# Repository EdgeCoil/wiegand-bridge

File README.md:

# Wiegand Bridge

Connect a standard **Wiegand keypad or card reader** to **Home Assistant**.

The reader plugs into this board, and the board sends every PIN and card it sees to Home Assistant
over Wi-Fi (ESPHome). Your automations decide what happens next: unlock a door, disarm an alarm,
or just log who came in.

> **Status: revision 10 is built, tested and working.** The files here are **revision 12**, which
> is routed and checked but not yet ordered: it adds a red/green status LED pair, cleans up the
> silkscreen, and moves the reader monitor and the RS-485 transceiver to integrated parts (see
> [`docs/design.md`](docs/design.md)). The tested design is tag
> [`rev-10b`](https://github.com/EdgeCoil/wiegand-bridge/tree/rev-10b).

## Why it only reports

**The board never unlocks anything.** It has no output to a lock. The reader sits outside the door
where anyone can reach it, so the part that actually opens the door stays inside, behind Home
Assistant. Prising the board off the wall and shorting wires opens nothing.

A stolen board can still give away your Wi-Fi passphrase and its Home Assistant API key, which
are in its flash. [`docs/design.md`](docs/design.md) (*Security — assume it gets stolen*) covers
the precautions: an isolated IoT network, checking the event's `device_id` in your automation, and
alerting on the tamper switch.

## How it works

```
 keypad / card reader ──Wiegand──▶ Wiegand Bridge ──Wi-Fi──▶ Home Assistant ──▶ your lock, alarm, …
          ▲                                │                       │
          └──── beep + LED feedback ◀──────┴──── "granted" / "denied" ┘
```

1. Someone enters a PIN (4–10 digits, then `#`) or presents a card.
2. The board sends a Home Assistant event, `esphome.wiegand_bridge`, with `type` set to `code` or
   `fob` and the PIN or card number in `value`.
3. Your automation checks it and does whatever you want.
4. It calls `feedback_granted` or `feedback_denied` on the board. *Granted* pulses the reader's LED
   three times and then holds it for 3 s; *denied* beeps three times. Both show on the screen, if fitted.

The keypad also works as a **doorbell**: pressing `#` with nothing typed fires the board's
`doorbell` event entity. While someone types, the board's `entry` sensor shows one `*` per digit
(never the digits). `*` clears an entry, and an entry too short to submit is cleared rather than
joined to the next one.

A minimal automation:

```yaml
triggers:
  - trigger: event
    event_type: esphome.wiegand_bridge
    event_data: { type: code }
conditions:
  - condition: template
    value_template: "{{ trigger.event.data.value == states('input_text.door_pin') }}"
actions:
  - action: esphome.wiegand_bridge_feedback_granted
  - action: lock.unlock
    target: { entity_id: lock.front_door }
```

## Getting started

1. **Order the board** (see [Ordering](#ordering)). JLCPCB assembles almost everything.
2. **Wire the reader** to the reader terminals: J3 (`+12V`, `GND`), J10 (`D0`, `D1`) and J11 (`LED`,
   `BEEP`, optional). Set the reader to 26-bit Wiegand. Wire colours vary between readers, so follow
   your reader's own leaflet. The full connector list is in [`docs/design.md`](docs/design.md).
3. **Power it** from 6–36 V (screw terminal or 5.5 mm barrel jack, centre positive), or from USB-C on
   the bench.
4. **Flash the firmware** over USB-C with ESPHome: [`firmware/wiegand-bridge.yaml`](firmware/wiegand-bridge.yaml).
   It needs four entries in your `secrets.yaml`: `wifi_ssid`, `wifi_password`,
   `wiegand_bridge_api_key` and `wiegand_bridge_ota_password`. If you've fitted the OLED, uncomment
   the `packages:` block at the end so it includes [`wiegand-bridge-oled.yaml`](firmware/wiegand-bridge-oled.yaml).
5. **Adopt it in Home Assistant** (ESPHome integration) and write your automation.

For the first power-up, follow the staged bench tests at the end of [`docs/design.md`](docs/design.md).

## Features

**Reader**
- Wiegand D0/D1 through a 5 V-tolerant Schmitt buffer, clamped against 12 V miswiring
- Open-drain LED and BEEP outputs back to the reader
- RS-485 port (THVD1420, fail-safe receiver) for OSDP readers, with jumper-selectable termination and bias

**Power**
- 6–36 V input, reverse-polarity and surge protected
- Regulated reader supply from every power source: 12.6 V (13.2 V by solder jumper), with current
  and voltage monitoring (INA226) and firmware-controlled shedding
- LiFePO4 backup: on-board charger (CN3058E, 3.6 V), cell protection (DW01A + FS8205A),
  thermistor-gated charging, seamless handover when external power drops

**Sensing and display**
- Tamper switch under the lid, plus a header for an enclosure-mounted one
- Four dry-contact inputs (door contact, exit button and so on), 24 V-tolerant
- Socket for a 1.3" SH1106 OLED (I²C), plus an SPI header for a TFT or e-paper

**Brains and expansion**
- ESP32-S3-WROOM-1-N8R2 with Wi-Fi and BLE; native USB-C for flashing and logs
- Status LEDs: red `FAULT` (warnings and errors) and green `OK` (connected to Home Assistant)
- TCA9535 expander for status lines and spares; Qwiic, W5500 Ethernet and 2×6 expansion headers
- SM712 surge and ESD protection on every field wire
- Optional relay footprint, **not fitted** by default (see *Security* in the design doc)

**Board:** 90 × 95 mm, 4 layers, assembled by JLCPCB.

## LITE (in development)

A 42 × 47 mm sibling for readers that already have their own supply: ESP32-S3-MINI-1, 8–16 V in,
USB-C, one 8-way pluggable terminal, and RS-485. Its D0/D1/LED/BEEP lines all work both ways, so it
can also pretend to be a reader towards an existing access controller.

**Designed, routed and checked, but no board made yet.** See [`docs/lite.md`](docs/lite.md),
[`hardware/lite/`](hardware/lite/) and [`firmware/wiegand-bridge-lite.yaml`](firmware/wiegand-bridge-lite.yaml).

| LITE | Next to the full board |
|---|---|
|  |  |

## What's in this repository

| Path | What it is |
|---|---|
| [`firmware/`](firmware/) | ESPHome configurations: the full board and its optional OLED package, the LITE, and a bench-only LITE emulation package |
| [`docs/design.md`](docs/design.md) | How it works, pin map, connectors, security notes and bench tests |
| [`docs/breadboard.md`](docs/breadboard.md) | A through-hole breadboard version, for trying your reader before ordering |
| [`docs/lite.md`](docs/lite.md) | The LITE board in detail |
| [`hardware/`](hardware/) | The board, **generated from Python** (`netlist.py` is the source of truth) |
| [`hardware/fab/`](hardware/fab/) | Ready-to-order files: Gerbers, BOM, placement, schematic and assembly PDFs, renders |
| [`hardware/sim/`](hardware/sim/) | ngspice checks of the analogue corners |
| [`hardware/lite/`](hardware/lite/) | The LITE board's scripts and outputs |

## Ordering

1. Upload `hardware/fab/wiegand-bridge-gerbers.zip` to JLCPCB and choose **4 layers** with
   **inner copper weight 1 oz**. JLCPCB's default for the inner layers is 0.5 oz, and the power rails
   and battery paths on In2 are sized for 1 oz (see *Layout* in the design doc).
2. Turn on **PCB Assembly**, top side, and upload `wiegand-bridge-bom.csv` and `wiegand-bridge-cpl.csv`.
3. **Check every polarised part in the placement preview** before confirming: diodes, LEDs, ICs,
   the ESP32 and the USB-C. Look especially at the status LEDs D8 and D23 (D8 changed footprint
   family in rev 11), U12 (INA226, MSOP-10), U9 (THVD1420), and the new U13 (TPS26625, VSON-10,
   0.5 mm pitch with an exposed pad; pin 1 top-left at rotation 0) and Q5 (DMP2035U, SOT-23).

JLCPCB doesn't fit the battery connector housing and cell, the OLED module, the barrel jack J14, or
any unpopulated headers. Add those yourself. J14's footprint is the DC-005 5.5 × 2.0 mm jack (LCSC
C16214), which LCSC lists at 12 V, 1 A: above 12 V use the screw terminal J2, or fit a jack rated
for your supply.

## Rebuilding the board

Everything under `hardware/` is produced by scripts, so the board can be rebuilt after any change.

| Script | What it does |
|---|---|
| `netlist.py` | Every part, its JLCPCB part number, and which net each pad joins |
| `placement.py` | Where each part sits |
| `build_pcb.py` | Makes `wiegand-bridge.kicad_pcb`, unrouted, from the two files above |
| `route.py` | Thermal vias, hand routes for the fine-pitch parts, GND fan-out, Freerouting, pours; fails on anything unconnected |
| `freeze.py`, `routing.json` | The frozen routing (since rev 12): `save` records the finished board's tracks and vias, `replay` lays them back |
| `padgap.py` | Pre-route: pads of different nets closer than 0.25 mm |
| `kelvin.py` | The reader shunt's Kelvin connection (net-tied sense tabs, own sense nets) |
| `stitch.py`, `via_fix.py`, `gndcheck.py`, `dfm_post.py`, `audit.py` | Stitching, vias out of pads, ground connectivity, paste and pours, mechanical and current audit |
| `finish_net.py` | Routes one straggling connection by grid A* if Freerouting leaves one |
| `schematic.py` | A readable schematic PDF from the netlist |
| `fab.py` | JLCPCB outputs into `fab/` |

The routing is **frozen**: `routing.json` holds every track and via of the reviewed board and a
rebuild replays it, so a fix is a small edit to that file rather than a new layout.

```bash
cd hardware
python3 build_pcb.py                       # needs KiCad 9's pcbnew Python module
python3 freeze.py replay                   # lay routing.json's copper back, rebuild the pours
python3 dfm_post.py
python3 kelvin.py                          # the shunt's sense lines are on their own copper
python3 gndcheck.py && python3 audit.py && python3 fab.py
kicad-cli pcb drc wiegand-bridge.kicad_pcb
```

Routing afresh, only when placement changes (the next review then covers all copper):

```bash
cd hardware
python3 build_pcb.py
python3 padgap.py 0.25                     # must report 0 pad pairs before routing
ROUTE_WORK=/tmp/wb python3 route.py 60     # needs Java + Freerouting 2.4.x; exits non-zero if anything is unconnected
python3 stitch.py && python3 stitch.py --islands
python3 via_fix.py --apply && python3 via_fix.py   # the second run must report 0 vias inside pad openings
python3 gndcheck.py
python3 dfm_post.py
python3 kelvin.py
python3 audit.py
python3 fab.py
kicad-cli pcb drc wiegand-bridge.kicad_pcb
python3 freeze.py save                     # record the copper in routing.json
```

Tools: KiCad 9.0, Freerouting 2.4.1 (OpenJDK), `easyeda2kicad` 1.0.1 (for `lib/`), ngspice 44.

<details>
<summary>3D models (not included)</summary>

The models come to about 60 MB, so they aren't in the repository, and the renders in `fab/` show
only the 0603/0805 passives: every other part renders as bare pads. To fetch them, run `easyeda2kicad --3d --lcsc_id=<part> --output hardware/lib/wb`
for the LCSC part numbers in the BOM. The 0603/0805 passives use KiCad's stock footprints, whose
models come from `kicad-packages3d`: `fab.py` looks for them in `~/.local/share/kicad/9.0/3dmodels`
(three files: `Resistor_SMD.3dshapes/R_0603_1608Metric`, `Capacitor_SMD.3dshapes/C_0603_1608Metric`
and `C_0805_2012Metric`, `.step` + `.wrl`, from gitlab.com/kicad/libraries/kicad-packages3D).

</details>

## Licence

| What | Licence |
|---|---|
| The board: everything in `hardware/`, including the scripts that define it (`netlist.py`, `placement.py`, `build_pcb.py`, `route.py`), the simulations and the fabrication outputs | [CERN-OHL-S-2.0](LICENSES/CERN-OHL-S-2.0.txt) |
| Firmware and the general-purpose build tools (every other script in `hardware/`) | [MIT](LICENSES/MIT.txt) |
| Documentation (`README.md`, `docs/`) and the renders | [CC BY 4.0](LICENSES/CC-BY-4.0.txt) |

Each source file carries an SPDX header, and [`REUSE.toml`](REUSE.toml) covers the rest by path.

CERN-OHL-S is strongly reciprocal. You may build, modify and sell boards from this design, but if
you ship a modified version you must publish its source under the same licence. The source lives at
https://github.com/EdgeCoil/wiegand-bridge, linked from the board's back silkscreen as
`wiegand.edgecoil.dev`.

**The edgecoil name and mark are not licensed.** Remove the mark from the silkscreen of any boards
you make or sell, and don't sell them under the edgecoil name.

The design is provided as is, with no warranty. It is an access-control accessory, so you are
responsible for the security of any installation.

---

edgecoil · [edgecoil.dev](https://edgecoil.dev)

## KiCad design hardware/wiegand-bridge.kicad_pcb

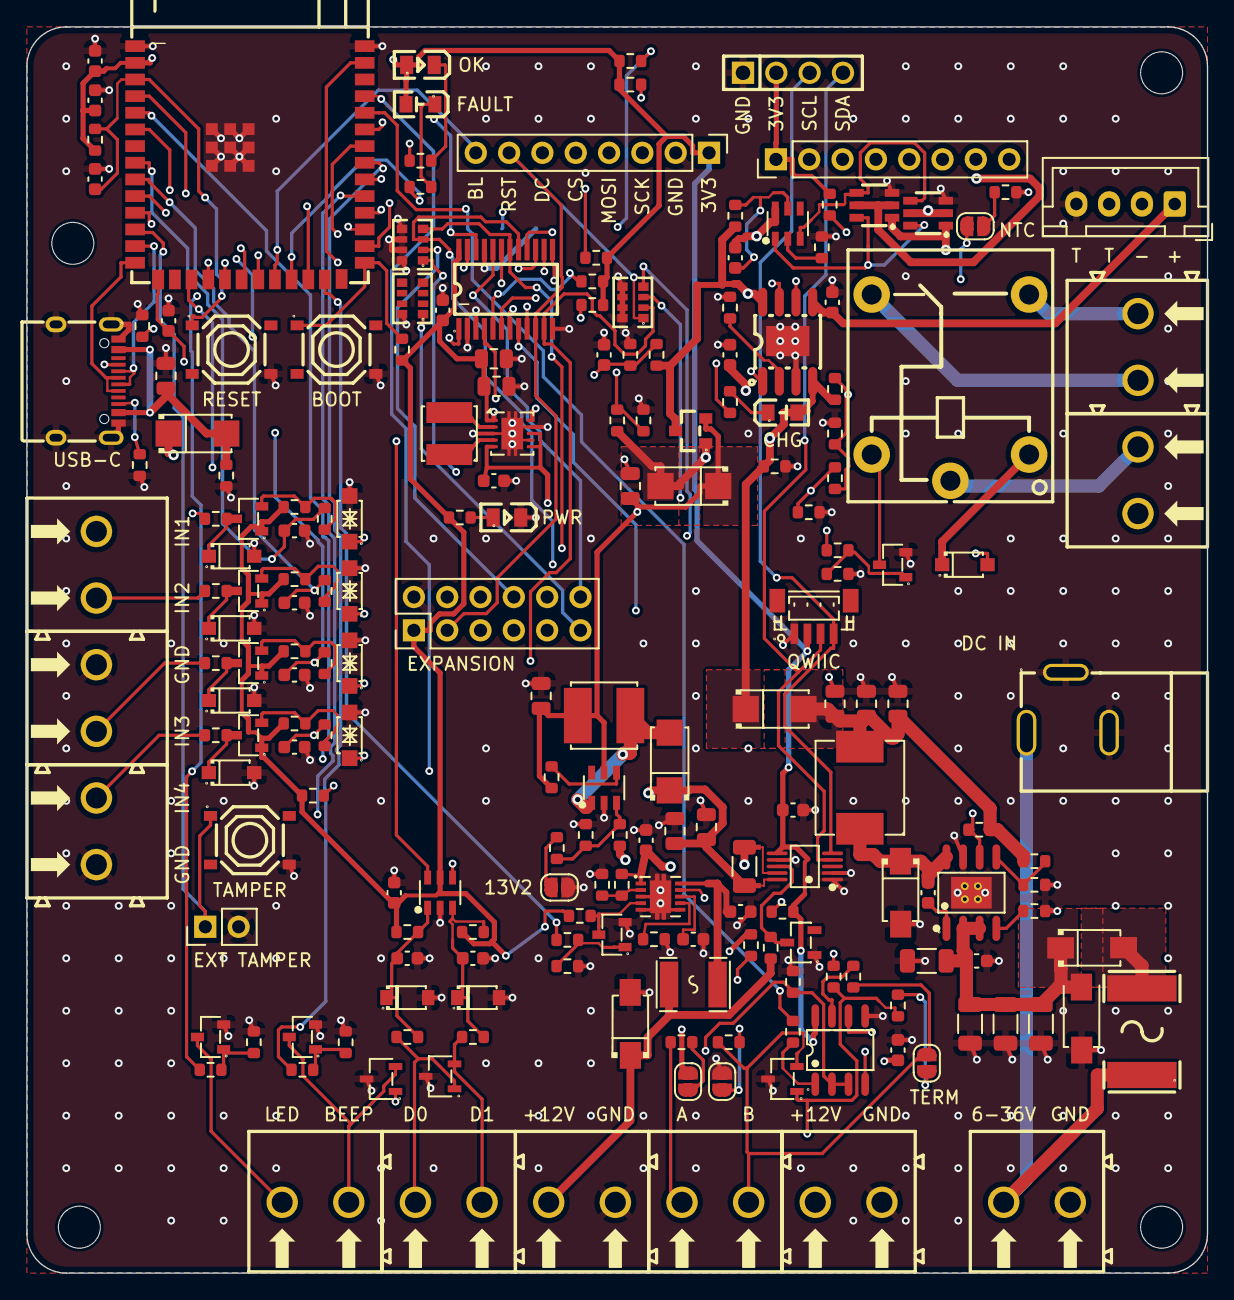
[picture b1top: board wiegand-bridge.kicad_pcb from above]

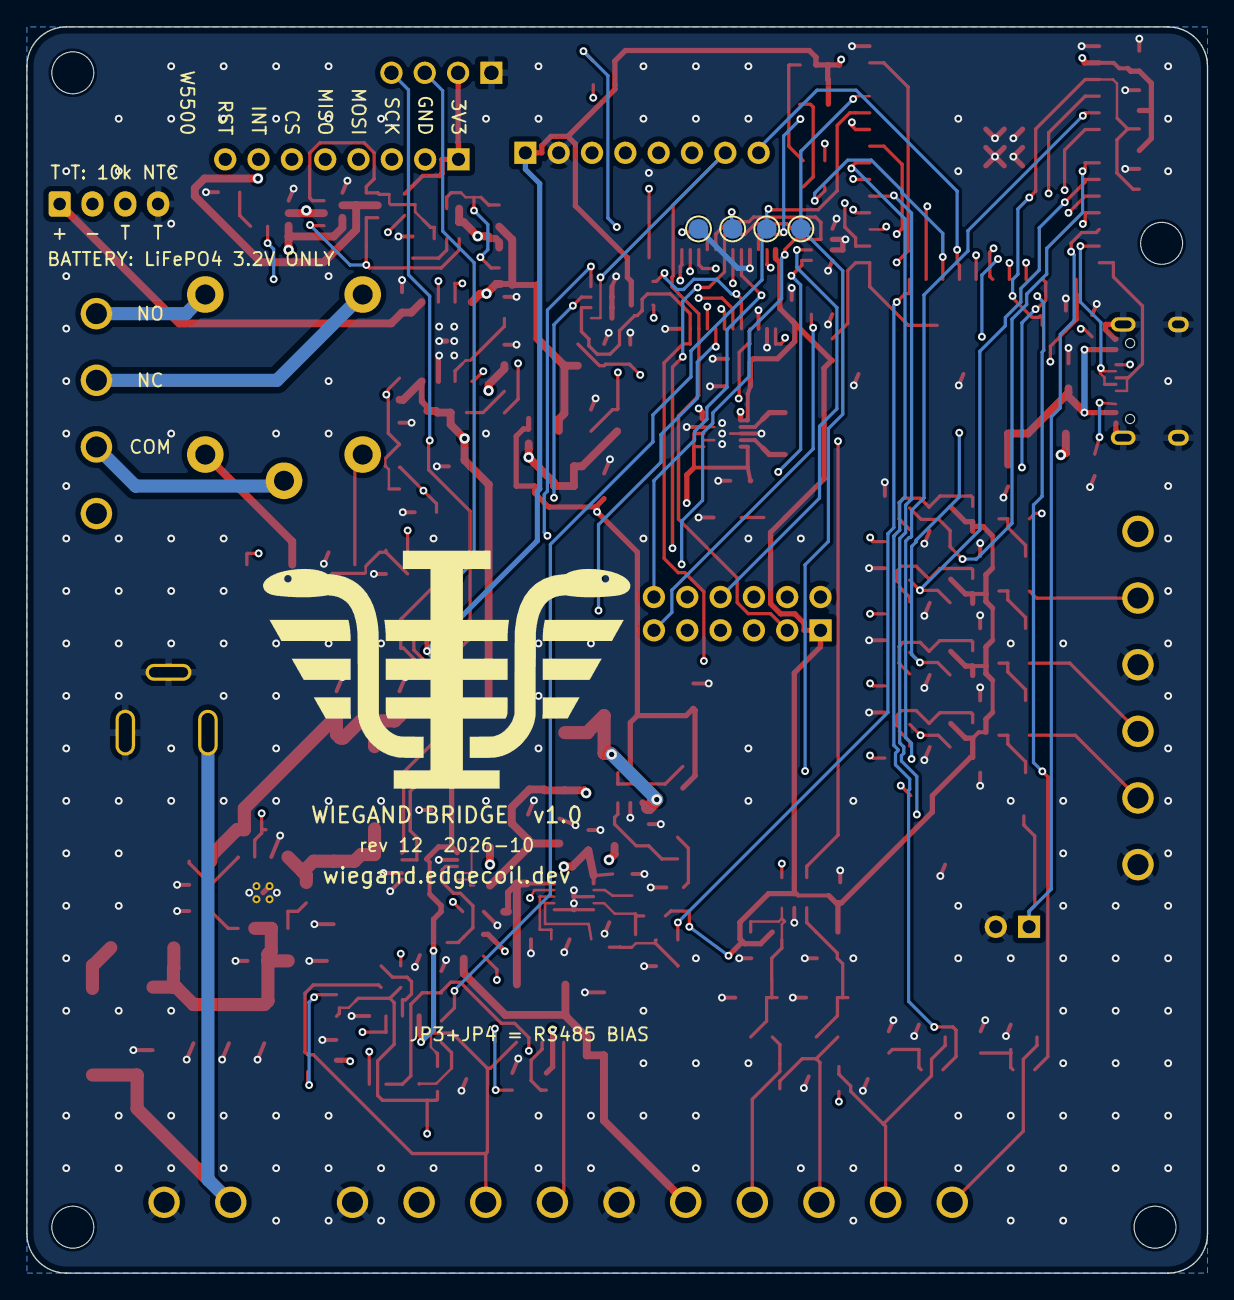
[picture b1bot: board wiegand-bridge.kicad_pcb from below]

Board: 4 copper layers, 90.0 x 95.0 mm, 208 parts (4 on the bottom side), 129 nets.

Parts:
C2, C31, C32, C33: 10u; C_1206_3216Metric
C3, C12, C16, C22, C23, C34, C36, C37, C39, C40, C41, C43: 100n; C_0603_1608Metric
C4, C5, C7, C9, C10, C17, C18, C19, C35: 22u; C_0805_2012Metric
C6: 10u; C_0805_2012Metric
C8, C20, C21: 10u; C_0603_1608Metric
C11: 22u; C_0603_1608Metric
C13: 1u; C_0603_1608Metric
C14, C15: 100p; C_0603_1608Metric
C27, C28, C29, C30: 10n; C_0603_1608Metric
C42: 680n; C_0603_1608Metric
D1, D13: SS56; SMA_L4.3-W2.6-LS5.0-RD
D2: SMAJ36CA; SMA_L4.3-W2.6-LS5.0-BI
D3, D4, D10, D11: SS34; SMA_L4.3-W2.6-LS5.2-RD
D5, D6: MMSZ5231B; SOD-123_L2.8-W1.6-LS3.7-RD
D7, D23: green; LED0805-R-RD
D8, D12: red; LED0805-RD
D14, D28, D29, D30, D31: 1N4148W; SOD-123F_L2.7-W1.6-LS3.8-RD
D15, D16, D19: SM712; SOT-23-3_L3.0-W1.7-P0.95-LS2.9-BR
D17, D18, D21, D22: SMF36CA; SOD-123FL_L2.7-W1.8-LS3.8-BI
D20: SMAJ15A; SMA_L4.3-W2.6-LS5.0-RD
D27: BAT54; SOT-23-3_L2.9-W1.4-P1.90-LS2.5-BR
F1: 0.5A; F1812
F2: 2A 60V; F2920
H1, H2, H3, H4: M3; MountingHole_3.2mm_M3
J1: USB-C; USB-C-SMD_TYPE-C-16PIN-2MD-073
J2: 6-36V IN; CONN-TH_P5.08_KF128-5.08-2P
J3: READER PWR; CONN-TH_P5.08_KF128-5.08-2P
J4: LiFePO4 + NTC; JST_XH_B4B-XH-A_1x04_P2.50mm_Vertical
J5: OLED SOCKET; HDR-TH_4P-P2.54-V-F
J6: TFT/EPD; PinHeader_1x08_P2.54mm_Vertical
J8: TAMPER EXT; PinHeader_1x02_P2.54mm_Vertical
J9: IN1 IN2; CONN-TH_P5.08_KF128-5.08-2P
J10: READER D0 D1; CONN-TH_P5.08_KF128-5.08-2P
J11: READER LED BEEP; CONN-TH_P5.08_KF128-5.08-2P
J12: GND IN3; CONN-TH_P5.08_KF128-5.08-2P
J13: IN4 GND; CONN-TH_P5.08_KF128-5.08-2P
J14: DC IN; DC-IN-TH_DC-005-5.5-2.0
J15: RELAY NC NO; CONN-TH_P5.08_KF128-5.08-2P
J16: RELAY COM; CONN-TH_P5.08_KF128-5.08-2P
J17: W5500; PinHeader_1x08_P2.54mm_Vertical
J18: QWIIC; CONN-SMD_BM04B-SRSS-TB
J19: EXPANSION; PinHeader_2x06_P2.54mm_Vertical
J20: RS485 A B; CONN-TH_P5.08_KF128-5.08-2P
J21: RS485 12V GND; CONN-TH_P5.08_KF128-5.08-2P
JP1: 13.2V; SolderJumper-2_P1.3mm_Open_RoundedPad1.0x1.5mm
JP2: TERM; SolderJumper-2_P1.3mm_Open_RoundedPad1.0x1.5mm
JP3, JP4: BIAS; SolderJumper-2_P1.3mm_Open_RoundedPad1.0x1.5mm
JP5: NTC ON BOARD; SolderJumper-2_P1.3mm_Open_RoundedPad1.0x1.5mm
K1: SRD-05VDC-SL-C; RELAY-TH_SRD-XXVDC-XL-C
L1: 15uH; IND-SMD_L7.0-W6.6_FXL0630
L2: 2.2uH; IND-SMD_L4.0-W4.0
L3: 4.7uH; IND-SMD_L5.0-W5.0
Q1, Q2, Q4, Q7, Q8, Q9, Q10: 2N7002; SOT-23-3_L2.9-W1.3-P1.90-LS2.4-BR
Q5: DMP2035U; SOT-23_L2.9-W1.3-P1.90-LS2.4-BR
Q6, Q13: FS8205A; SOT-23-6_L2.9-W1.6-P0.95-LS2.8-BR
Q12: AO3400A; SOT-23-3_L2.9-W1.3-P1.90-LS2.4-BR
R1, R2, R77: 5.1k; R_0603_1608Metric
R3, R81: 470; R_0603_1608Metric
R4, R5, R15, R18, R20, R27, R35, R50, R60, R65, R75, R76, R90, R91, R92, R93, R97: 10k; R_0603_1608Metric
R6, R7, R17, R25: 100; R_0603_1608Metric
R8, R9, R10, R24, R26, R63, R85, R94: 1k; R_0603_1608Metric
R11, R12: 22k; R_0603_1608Metric
R13, R14, R21, R28, R29, R58, R61, R62, R64, R79, R99: 100k; R_0603_1608Metric
R16: 15k; R_0603_1608Metric
R19, R30, R80: 200k; R_0603_1608Metric
R36, R37, R40, R41, R42, R43, R82: 4.7k; R_0603_1608Metric
R44, R45, R46, R47, R56: 47k; R_0603_1608Metric
R51: 1M; R_0603_1608Metric
R55: 39k; R_0603_1608Metric
R57: 8.2k; R_0603_1608Metric
R59: 0.1R; R_1206_Kelvin
R68: 120; R_0603_1608Metric
R72, R73: 390; R_0603_1608Metric
R78: 68k; R_0603_1608Metric
R83, R84: 10; R_0603_1608Metric
R95: 26.7k; R_0603_1608Metric
R96: 120k; R_0603_1608Metric
RN1, RN2, RN3: 4x10k; RES-ARRAY-SMD_0603-8P-L3.2-W1.6-BL
RT1: 10k NTC B3950; R_0603_1608Metric
SW1: BOOT; SW-SMD_4P-L5.1-W5.1-P3.70-LS6.5-TL_H1.5
SW2: RESET; SW-SMD_4P-L5.1-W5.1-P3.70-LS6.5-TL_H1.5
SW3: TAMPER; SW-SMD_4P-L5.1-W5.1-P3.70-LS6.5-TL_H1.5
TP1: RS485_DI; TestPoint_Pad_D1.5mm
TP2: RS485_RXD; TestPoint_Pad_D1.5mm
TP3: IO40; TestPoint_Pad_D1.5mm
TP4: GND; TestPoint_Pad_D1.5mm
U1: ESP32-S3-WROOM-1-N8R2; WIRELM-SMD_ESP32-S3-WROOM-1
U2: LMR16020; SOIC-8_L4.9-W3.9-P1.27-LS6.0-BL-EP
U3: TPS63001; Texas_DRC0010J
U4: SN74LVC2G17; SOT-23-6_L2.9-W1.6-P0.95-LS2.8-BL
U5: CN3058E; SOIC-8_L4.9-W3.9-P1.27-LS6.0-BL-EP3.3
U6: MT3608; SOT-23-6_L2.9-W1.6-P0.95-LS2.8-BL
U7: DW01A; SOT-23-6_L2.9-W1.6-P0.95-LS2.8-BL
U8: TCA9535; TSSOP-24_L7.8-W4.4-P0.65-LS6.4-BL
U9: THVD1420; SOIC-8_L4.9-W3.9-P1.27-LS6.0-BL
U12: INA226; MSOP-10_L3.0-W3.0-P0.50-LS5.0-BL
U13: TPS26625; VSON-10_L3.0-W3.0-P0.50-TL-EP-1

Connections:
+3V3: C9.1, C10.1, C11.1, C12.1, C16.1, C36.1, C37.1, C39.1, D8.2, D23.1, J5.2, J6.1, J17.1, J18.2, J19.1, JP3.2, Q7.1, Q8.1, Q9.1, Q10.1, R3.1, R4.1, R5.1, R11.1, R12.1, R35.1, R36.1, R37.1, R44.1, R45.1, R46.1, R47.1, R60.2, R61.2, R62.2, R75.2, R76.2, R97.2, R99.1, U1.2, U3.1, U3.10, U4.5, U8.24, U9.8, U12.6
+5V: C20.1, D3.1, D4.1, D11.2, D12.2, D14.1, K1.1, Q5.1, R15.1, R27.1, R77.1, U5.4
+5V_BUCK: C4.1, C5.1, C35.1, D3.2, L1.2, R56.1, R58.2
+12V_RDR: D20.1, F1.2, J3.1, J21.1, R82.1
+VIN: C2.1, C31.1, C32.1, C33.1, C34.1, D1.1, D2.1, U2.2, U2.3
+VIN_F: D1.2, F2.2
+VIN_RAW: F2.1, J2.1, J14.4
BAT+: C21.1, J4.1, Q5.3, R25.1, R28.1, U5.5, U5.8
BAT-: C22.2, J4.2, Q6.1, Q13.1, U7.6
BAT_SENSE: C23.1, R28.2, R29.1, U1.39
BAT_TEMP: J4.3, JP5.1, R77.2, R78.1, R79.1, U5.1
BEEP_GATE: Q2.1, R7.2, R14.1
BOOST_FB: R19.2, R20.1, R30.1, U6.3
BOOST_OUT: C18.1, C19.1, D10.1, R19.1, R59.1
BOOST_SNS: C41.1, R51.1, R59.2, U13.1
BOOST_SW: D10.2, L3.2, U6.1
CC1: J1.A5, R1.1
CC2: J1.B5, R2.1
CHRG: R24.1, R61.1, U5.7, U8.5
D0_IN: C14.1, D5.1, R9.2, R11.2, U4.1
D0_RAW: D15.1, J10.1, R9.1
D1_IN: C15.1, D6.1, R10.2, R12.2, U4.3
D1_RAW: D15.2, J10.2, R10.1
D7_A: D7.1, R3.2
D8_K: D8.1, R8.2
D12_K: D12.1, R24.2
D23_K: D23.2, R81.2
DISP_RST: J6.7, J19.3, RN1.1, U8.10
DONE_N: R62.1, U5.6, U8.6
EN: C13.1, R4.2, SW2.1, U1.3
ETH_CS: J17.6, U1.29
ETH_INT: J17.7, U1.30
ETH_MISO: J17.5, U1.28
ETH_RST: J17.8, R76.1, U8.9
EXP07: J19.4, RN1.2, U8.11
EXP10: J19.5, RN1.3, U8.13
EXP11: J19.6, RN1.4, U8.14
EXP12: J19.7, RN2.1, U8.15
EXP13: J19.8, RN2.2, U8.16
EXP14: J19.9, RN2.3, U8.17
EXP15: J19.10, RN2.4, U8.18
EXP16: J19.11, RN3.1, U8.19
EXP17: J19.12, U8.20
EXP_INT: R60.1, U1.32, U8.1
EXT_SENSE: R15.2, R16.1, U8.7
GND: C2.2, C4.2, C5.2, C6.2, C7.2, C8.2, C9.2, C10.2, C11.2, C12.2, C13.2, C14.2, C15.2, C16.2, C17.2, C18.2, C19.2, C20.2, C21.2, C23.2, C27.2, C28.2, C29.2, C30.2, C31.2, C32.2, C33.2, C34.2, C35.2, C36.2, C37.2, C39.2, C40.2, C41.2, C42.2, C43.2, D2.2, D5.2, D6.2, D7.2, D13.2, D15.3, D16.3, D17.2, D18.2, D19.3, D20.2, D21.2, D22.2, D27.1, D28.2, D29.2, D30.2, D31.2, J1.13, J1.14, J1.A1B12, J1.B1A12, J2.2, J3.2, J4.4, J5.1, J6.2, J8.2, J12.1, J13.2, J14.2, J14.3, J17.2, J18.1, J19.2, J21.2, JP1.2, JP4.2, Q1.2, Q2.2, Q4.2, Q6.3, Q12.2, Q13.3, R1.2, R2.2, R13.2, R14.2, R16.2, R18.2, R20.2, R26.2, R27.2, R29.2, R50.2, R55.2, R57.2, R64.2, R65.2, R78.2, R80.2, R94.2, R95.2, R96.2, RN1.5, RN1.6, RN1.7, RN1.8, RN2.5, RN2.6, RN2.7, RN2.8, RN3.8, RT1.2, SW1.4, SW2.4, SW3.4, TP4.1, U1.1, U1.40, U1.41, U2.7, U2.9, U3.3, U3.7, U3.9, U3.11, U4.2, U5.3, U5.9, U6.2, U8.2, U8.3, U8.12, U8.21, U9.5, U12.1, U12.2, U12.7, U13.3, U13.5, U13.6, U13.11
I2C_SCL: J5.3, J18.4, R37.2, U1.35, U8.22, U12.5
I2C_SDA: J5.4, J18.3, R36.2, U1.34, U8.23, U12.4
IN1: C27.1, R90.2, U1.8
IN1_D: D28.1, Q7.3, R40.2
IN1_RAW: D17.1, J9.1, R40.1
IN1_S: Q7.2, R44.2, R90.1
IN2: C28.1, R91.2, U1.9
IN2_D: D29.1, Q8.3, R41.2
IN2_RAW: D18.1, J9.2, R41.1
IN2_S: Q8.2, R45.2, R91.1
IN3: C29.1, R92.2, U1.10
IN3_D: D30.1, Q9.3, R42.2
IN3_RAW: D21.1, J12.2, R42.1
IN3_S: Q9.2, R46.2, R92.1
IN4: C30.1, R93.2, U1.11
IN4_D: D31.1, Q10.3, R43.2
IN4_RAW: D22.1, J13.1, R43.1
IN4_S: Q10.2, R47.2, R93.1
IO0: R5.2, SW1.1, U1.27
IO6: R6.1, U1.6
IO21: R8.1, U1.23
IO40: R7.1, TP3.1, U1.33
IO47: R81.1, U1.24
IO48: R17.1, U1.25
ISET: R50.1, U5.2
ISNS_N: R59.4, U12.9
ISNS_P: R59.3, U12.10
JP1_A: JP1.1, R30.2
JP2_A: JP2.1, R68.2
JP3_A: JP3.1, R72.2
JP4_A: JP4.1, R73.2
LED_GATE: Q1.1, R6.2, R13.1
OC: Q6.4, Q13.4, U7.3
OD: Q6.6, Q13.6, U7.1
PGOOD5: R58.1, U2.6, U8.8
Q4_G: Q4.1, R17.2, R18.1
Q6_D: Q6.2, Q6.5, Q13.2, Q13.5
Q12_G: Q12.1, R63.2, R64.1
RDR_BEEP: D16.2, J11.2, Q2.3
RDR_EN: Q4.3, R99.2, U13.4
RDR_FLT: R97.1, U1.17, U13.9
RDR_LED: D16.1, J11.1, Q1.3
RDR_SW: C43.1, F1.1, U13.10
RDR_VBUS: D27.3, R82.2, U12.8
RELAY_COIL: D14.2, K1.4, Q12.3
RELAY_COM: J16.2, K1.5
RELAY_DRV: R63.1, U8.4
RELAY_NC: J15.1, K1.3
RELAY_NO: J15.2, K1.2
RS485_A: D19.1, J20.1, R68.1, R72.1, R83.1
RS485_B: D19.2, J20.2, JP2.2, R73.1, R84.1
RS485_DE: R65.1, U1.31, U9.2, U9.3
RS485_DI: TP1.1, U1.37, U9.4
RS485_RO: R85.1, U9.1
RS485_RXD: R75.1, R85.2, TP2.1, U1.36
RT1_A: JP5.2, RT1.1
SPI_BL_BUSY: J6.8, U1.22
SPI_CS: J6.5, U1.18
SPI_DC: J6.6, U1.21
SPI_MOSI: J6.4, J17.4, U1.19
SPI_SCK: J6.3, J17.3, U1.20
TAMPER: J8.1, R35.2, SW3.1, U1.12
TEMP_ADC: C40.1, R79.2, R80.1, U1.15
U2_BST: C3.1, U2.1
U2_FB: R56.2, R57.1, U2.5
U2_RT: R55.1, U2.4
U2_SW: C3.2, D13.1, L1.1, U2.8
U3_L1: L2.1, U3.4
U3_L2: L2.2, U3.2
U6_EN: R21.2, U6.4
U7_VCC: C22.1, R25.2, U7.5
U9_A: R83.2, U9.6
U9_B: R84.2, U9.7
U13_DVDT: C42.1, U13.8
U13_ILIM: R95.1, U13.7
U13_UVLO: R51.2, R96.1, U13.2
USB_DN: J1.A7, J1.B7, U1.13
USB_DP: J1.A6, J1.B6, U1.14
VBUS: C6.1, D4.2, J1.A4B9, J1.B4A9, R94.1
VM: R26.1, U7.2
VSYS: C7.1, C8.1, C17.1, D11.1, L3.1, Q5.2, R21.1, U3.5, U3.6, U3.8, U6.5
WG_D0: U1.4, U4.6
WG_D1: U1.5, U4.4

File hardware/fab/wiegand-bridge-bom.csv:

Comment,Designator,Footprint,LCSC Part #
22u,C11,C_0603_1608Metric,C59461
1u,C13,C_0603_1608Metric,C15849
100p,"C14,C15",C_0603_1608Metric,C14858
10n,"C27,C28,C29,C30",C_0603_1608Metric,C57112
10u,"C2,C31,C32,C33",C_1206_3216Metric,C13585
100n,"C3,C12,C16,C22,C23,C34,C36,C37,C39,C40,C41,C43",C_0603_1608Metric,C14663
22u,"C4,C5,C7,C9,C10,C17,C18,C19,C35",C_0805_2012Metric,C45783
680n,C42,C_0603_1608Metric,C107067
10u,C6,C_0805_2012Metric,C15850
10u,"C8,C20,C21",C_0603_1608Metric,C19702
SS56,"D1,D13",SMA_L4.3-W2.6-LS5.0-RD,C18199169
SM712,"D15,D16,D19",SOT-23-3_L3.0-W1.7-P0.95-LS2.9-BR,C32677
SMF36CA,"D17,D18,D21,D22",SOD-123FL_L2.7-W1.8-LS3.8-BI,C19077521
SMAJ36CA,D2,SMA_L4.3-W2.6-LS5.0-BI,C19077551
SMAJ15A,D20,SMA_L4.3-W2.6-LS5.0-RD,C19077535
BAT54,D27,SOT-23-3_L2.9-W1.4-P1.90-LS2.5-BR,C22466368
1N4148W,"D14,D28,D29,D30,D31",SOD-123F_L2.7-W1.6-LS3.8-RD,C81598
SS34,"D3,D4,D10,D11",SMA_L4.3-W2.6-LS5.2-RD,C8678
MMSZ5231B,"D5,D6",SOD-123_L2.8-W1.6-LS3.7-RD,C19077422
green,"D7,D23",LED0805-R-RD,C2297
red,"D8,D12",LED0805-RD,C84256
0.5A,F1,F1812,C516067
2A 60V,F2,F2920,C49326266
USB-C,J1,USB-C-SMD_TYPE-C-16PIN-2MD-073,C2765186
KF128-5.08-2P screw terminal,"J2,J3,J9,J10,J11,J12,J13,J20,J21",CONN-TH_P5.08_KF128-5.08-2P,C474952
LiFePO4 + NTC,J4,JST_XH_B4B-XH-A_1x04_P2.50mm_Vertical,C144395
OLED SOCKET,J5,HDR-TH_4P-P2.54-V-F,C2718488
15uH,L1,IND-SMD_L7.0-W6.6_FXL0630,C177243
2.2uH,L2,IND-SMD_L4.0-W4.0,C279948
4.7uH,L3,IND-SMD_L5.0-W5.0,C305174
2N7002,"Q1,Q2,Q4,Q7,Q8,Q9,Q10",SOT-23-3_L2.9-W1.3-P1.90-LS2.4-BR,C8545
AO3400A,Q12,SOT-23-3_L2.9-W1.3-P1.90-LS2.4-BR,C20917
DMP2035U,Q5,SOT-23_L2.9-W1.3-P1.90-LS2.4-BR,C110499
FS8205A,"Q6,Q13",SOT-23-6_L2.9-W1.6-P0.95-LS2.8-BR,C2830320
5.1k,"R1,R2,R77",R_0603_1608Metric,C23186
22k,"R11,R12",R_0603_1608Metric,C31850
10k,"R4,R5,R15,R18,R20,R27,R35,R50,R60,R65,R75,R76,R90,R91,R92,R93,R97",R_0603_1608Metric,C25804
15k,R16,R_0603_1608Metric,C22809
200k,"R19,R30,R80",R_0603_1608Metric,C25811
470,"R3,R81",R_0603_1608Metric,C23179
4.7k,"R36,R37,R82",R_0603_1608Metric,C23162
4.7k,"R40,R41,R42,R43",R_0603_1608Metric,C844791
1M,R51,R_0603_1608Metric,C22935
39k,R55,R_0603_1608Metric,C23153
47k,"R44,R45,R46,R47,R56",R_0603_1608Metric,C25819
8.2k,R57,R_0603_1608Metric,C25981
100k,"R13,R14,R21,R28,R29,R58,R61,R62,R64,R79,R99",R_0603_1608Metric,C25803
0.1R,R59,R_1206_Kelvin,C201308
100,"R6,R7,R17,R25",R_0603_1608Metric,C22775
120,R68,R_0603_1608Metric,C22787
390,"R72,R73",R_0603_1608Metric,C23151
68k,R78,R_0603_1608Metric,C23231
10,"R83,R84",R_0603_1608Metric,C844519
1k,"R8,R9,R10,R24,R26,R63,R85,R94",R_0603_1608Metric,C21190
26.7k,R95,R_0603_1608Metric,C22923
120k,R96,R_0603_1608Metric,C25808
4x10k,"RN1,RN2,RN3",RES-ARRAY-SMD_0603-8P-L3.2-W1.6-BL,C29718
10k NTC B3950,RT1,R_0603_1608Metric,C2892547
TS-1187A tact switch,"SW1,SW2,SW3",SW-SMD_4P-L5.1-W5.1-P3.70-LS6.5-TL_H1.5,C318884
ESP32-S3-WROOM-1-N8R2,U1,WIRELM-SMD_ESP32-S3-WROOM-1,C2913204
INA226,U12,MSOP-10_L3.0-W3.0-P0.50-LS5.0-BL,C49851
TPS26625,U13,VSON-10_L3.0-W3.0-P0.50-TL-EP-1,C2862873
LMR16020,U2,SOIC-8_L4.9-W3.9-P1.27-LS6.0-BL-EP,C190006
TPS63001,U3,Texas_DRC0010J,C28060
SN74LVC2G17,U4,SOT-23-6_L2.9-W1.6-P0.95-LS2.8-BL,C10429
CN3058E,U5,SOIC-8_L4.9-W3.9-P1.27-LS6.0-BL-EP3.3,C112011
MT3608,U6,SOT-23-6_L2.9-W1.6-P0.95-LS2.8-BL,C84817
DW01A,U7,SOT-23-6_L2.9-W1.6-P0.95-LS2.8-BL,C351410
TCA9535,U8,TSSOP-24_L7.8-W4.4-P0.65-LS6.4-BL,C130204
THVD1420,U9,SOIC-8_L4.9-W3.9-P1.27-LS6.0-BL,C3235215

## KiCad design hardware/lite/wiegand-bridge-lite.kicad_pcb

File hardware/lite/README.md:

# Wiegand bridge LITE — board files

The small board for `docs/lite.md` (design, reasoning, what was dropped from the
full board and why). A sibling of `../` (the full board): same code-generated flow, its own
`netlist.py` and `placement.py`, and the pipeline scripts **copied and trimmed** rather than shared —
every script in the full board's tree hard-codes its board name and part references, and the live
rev 11 tree was not worth refactoring for this.

| File | What it is |
|---|---|
| `netlist.py` | **Source of truth**: every part, its JLCPCB part number and which net each pad joins |
| `placement.py` | Where each part sits (board 42 × 47 mm since rev 2) |
| `build_pcb.py` | Makes `wiegand-bridge-lite.kicad_pcb`, unrouted, from the two files above |
| `route.py` | Thermal vias under the module, the USB-C VBUS pad-pair hand route, GND fan-out, Freerouting, ground pours; fails on anything unconnected |
| `freeze.py`, `routing.json` | The frozen routing: `save` records the finished board's tracks and vias, `replay` lays them back after `build_pcb.py` |
| `padgap.py` | Pre-route: pads of different nets closer than 0.25 mm (new for this board) |
| `verify.py` | **Every file-based check in one run** (DRC, audit, pad gaps, joint spacing, silk sizes, firmware↔netlist, polarity, open pads, BOM/CPL/gerbers, JLCPCB classes and stock); `--offline` skips the library query |
| `stitch.py`, `via_fix.py`, `gndcheck.py`, `dfm_post.py`, `audit.py` | Post-route, as the full board; `audit.py` has no screen/battery sections |
| `schematic.py`, `fab.py`, `finish_net.py`, `widen.py`, `plane_connect.py` | As the full board, names changed |
| `wiegand-bridge-lite.kicad_pro` | **Carries the netclasses** (signals 0.2 mm / 0.15 mm, power 0.5 mm): without it `kicad-cli pcb drc` falls back to 0.2 mm clearance and reports ~90 false clearance errors (seen 2026-10-21 when the project file was left out of a copy) |
| `lib/`, `art/` | **Symlinks** into `../` (the full board) — one footprint library (the new parts were fetched into it) and one mark |

Differences from the full board's scripts, so a diff is not a surprise: 2 mounting holes; the
MINI-1's nine centre GND pads take the thermal vias (no exposed pads anywhere else, so `dfm_post`
has no paste windows); `route.py` pre-routes the USB-C VBUS pair, USB D+/D-, U2/C2's ground link and R87's stub (see docs/lite.md, Layout); `fab.py` has no rotation or body-centre
fixes (every footprint is EasyEDA-sourced except the 0603/0805 passives, the solder jumper and the
holes).

## Rebuild

The routing is **frozen** (since rev 2): `routing.json` holds every track and via of the reviewed
board, and a rebuild replays it, so a fix is a small edit to that file rather than a new layout.

```bash
python3 build_pcb.py                 # system python3: KiCad 9's pcbnew module
python3 freeze.py replay             # lay routing.json's copper back, rebuild the GND pours
python3 dfm_post.py                  # copper round D1/D3
python3 gndcheck.py && python3 audit.py && python3 fab.py && python3 schematic.py   # fab.py also writes the 1:1 PDF
python3 verify.py                    # must end ALL CHECKS PASSED
```

Routing afresh, only when placement changes (the next review then covers all copper):

```bash
python3 build_pcb.py                 # system python3: KiCad 9's pcbnew module
python3 audit.py --silk              # labels vs pads/outlines/bodies/edge: iterate before routing
python3 padgap.py 0.25               # pads of different nets closer than 0.25 mm: MUST be 0 before routing
ROUTE_WORK=/tmp/wbl python3 route.py 60             # 30 passes was not enough here; exits non-zero if anything is unconnected
python3 widen.py                     # power tracks to 0.5 mm where DRC allows
python3 stitch.py && python3 stitch.py --islands
python3 via_fix.py --apply && python3 via_fix.py   # the second run must report 0 vias inside pad openings
python3 gndcheck.py                  # run from this directory
python3 dfm_post.py                  # copper round D1/D3
python3 audit.py
python3 fab.py                       # clears fab/ (keeping size-comparison.png) and writes the 1:1 PDF; regenerate the schematic after
python3 schematic.py
kicad-cli pcb drc wiegand-bridge-lite.kicad_pcb
python3 verify.py                    # everything above plus the cross-checks; must end ALL CHECKS PASSED
python3 freeze.py save               # record the copper in routing.json
```

`route.py` keeps rule areas (the antenna keep-out) through routing and exits non-zero if anything is
left unconnected; re-run it from `build_pcb.py` until it exits 0.

**Space parts by pad extents, not courtyards.** KiCad's 0603 courtyard is 3.0 × 1.5 mm (generous)
while the EasyEDA footprints' courtyards stop short of their pad ends (the SMA, SOT-23 and TSOT pads
run up to 0.9 mm past them), so a courtyard check passed three placements whose pads overlapped and
whose routes failed on exactly those pads. `padgap.py` is the check; the 12 remaining
`courtyards_overlap` DRC warnings between cell passives are accepted (pads ≥ 0.25 mm apart).
`route.py` also pre-routes the USB-C's VBUS pad pair, which Freerouting never joins.

## Ordering at JLCPCB

Upload `fab/wiegand-bridge-lite-gerbers.zip`, choose PCB Assembly (top side), then upload the BOM
and CPL. **Check every polarised part's rotation in the CPL previewer** — the three LEDs, the
diodes (pad 1 = cathode on every SMA and SOD-123 part, except D2, which is bidirectional), the ICs, the module, the
USB-C. The terminal J3 is through-hole: either add JLCPCB's THT assembly or leave it off the BOM
and solder it by hand. The mating plug (KF2EDGK-3.5-8P) is not on the BOM; buy it separately.

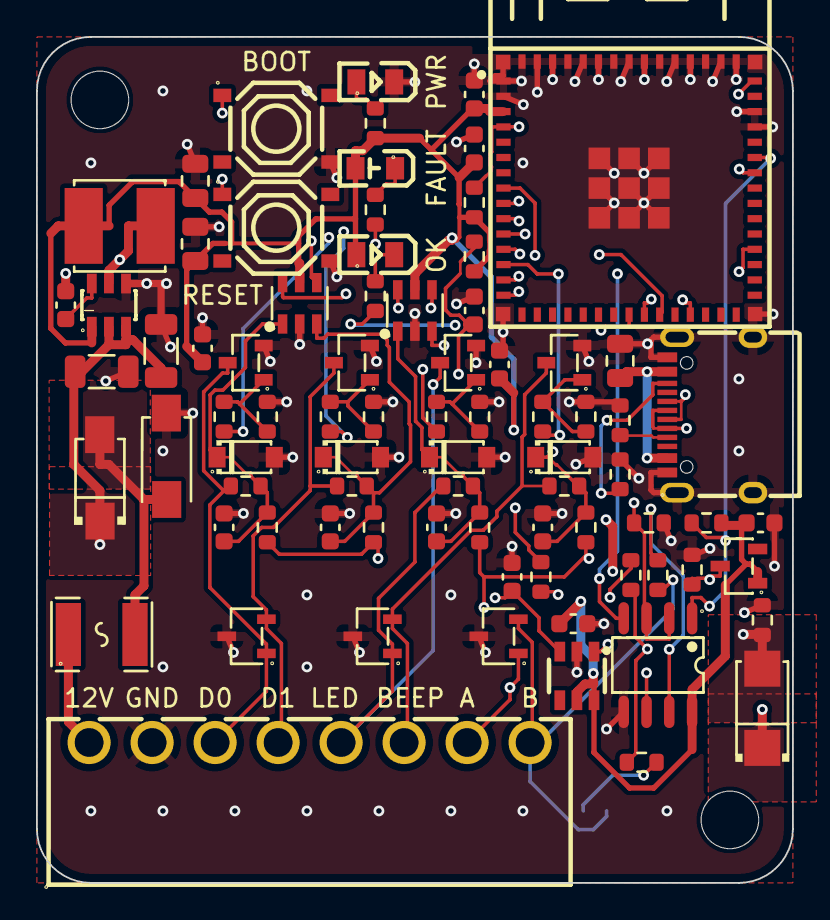
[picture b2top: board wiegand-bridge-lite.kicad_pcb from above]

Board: 4 copper layers, 42.0 x 47.0 mm, 82 parts (1 on the bottom side), 50 nets.

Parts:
C1, C2: 10u; C_1206_3216Metric
C3, C12, C16, C37, C41, C44: 100n; C_0603_1608Metric
C4, C5: 22u; C_0805_2012Metric
C6: 10u; C_0805_2012Metric
C11: 22u; C_0603_1608Metric
C13: 1u; C_0603_1608Metric
C14, C15, C42, C43: 100p; C_0603_1608Metric
C45: 10n; C_0603_1608Metric
D1: SS56; SMA_L4.3-W2.6-LS5.0-RD
D2: SMAJ18CA; SMA_L4.3-W2.6-LS5.0-BI
D3: SS34; SMA_L4.3-W2.6-LS5.2-RD
D5, D6, D24, D25: MMSZ5231B; SOD-123_L2.8-W1.6-LS3.7-RD
D7, D23: green; LED0805-R-RD
D8: red; LED0805-RD
D15, D16, D19: SM712; SOT-23-3_L3.0-W1.7-P0.95-LS2.9-BR
D26: BAT54; SOT-23-3_L2.9-W1.4-P1.90-LS2.5-BR
F1: 0.5A 24V; F1812
H1, H2: M3; MountingHole_3.2mm_M3
J1: USB-C; USB-C-SMD_TYPE-C-16PIN-2MD-073
J3: 12V GND D0 D1 LED BEEP A B; CONN-TH_8P-P3.50_KF2EDGR-3.5-8P
JP2: TERM; SolderJumper-2_P1.3mm_Open_RoundedPad1.0x1.5mm
L1: 4.7uH; IND-SMD_L5.0-W5.0
Q1, Q2, Q3, Q4: AO3400A; SOT-23-3_L2.9-W1.3-P1.90-LS2.4-BR
R1, R2: 5.1k; R_0603_1608Metric
R3, R81: 470; R_0603_1608Metric
R4, R5, R65, R75: 10k; R_0603_1608Metric
R6, R7, R24, R26: 100; R_0603_1608Metric
R8, R9, R10, R20, R21, R86, R87: 1k; R_0603_1608Metric
R11, R12, R22, R23: 22k; R_0603_1608Metric
R13, R14, R25, R27: 100k; R_0603_1608Metric
R68: 120; R_0603_1608Metric
R88, R89: 10; R_0603_1608Metric
R95: 4.7k; R_0603_1608Metric
SW1: BOOT; SW-SMD_4P-L5.1-W5.1-P3.70-LS6.5-TL_H1.5
SW2: RESET; SW-SMD_4P-L5.1-W5.1-P3.70-LS6.5-TL_H1.5
U1: ESP32-S3-MINI-1-N4R2; BULETM-SMD_ESP32-S3-MINI-1-N8
U2: AP63203; TSOT-26_L2.9-W1.6-P0.95-LS2.8-BL
U3: TPS3808G30; SOT-23-6_L2.9-W1.6-P0.95-LS2.8-BR
U4, U11: SN74LVC2G17; SOT-23-6_L2.9-W1.6-P0.95-LS2.8-BL
U9: THVD1420; SOIC-8_L4.9-W3.9-P1.27-LS6.0-BL

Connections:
+3V3: C4.1, C5.1, C11.1, C12.1, C16.1, C37.1, C41.1, C44.1, D8.2, D23.1, D26.1, L1.2, R3.1, R4.1, R5.1, R75.2, U1.3, U2.1, U3.5, U3.6, U4.5, U9.8, U11.5
+3V3_PU: D26.3, R11.1, R12.1, R22.1, R23.1, R95.1
+VIN: C1.1, C2.1, D1.1, D3.1, U2.2, U2.3
+VIN_F: D1.2, D2.1, F1.2
+VIN_RAW: F1.1, J3.1
BEEP_IN: C43.1, D25.1, R21.2, R23.2, U11.3
BEEP_RX: U1.15, U11.4
BEEP_TX: R7.1, U1.13
CC1: J1.A5, R1.1
CC2: J1.B5, R2.1
D0_IN: C14.1, D5.1, R9.2, R11.2, U4.1
D0_RAW: D15.1, J3.3, Q3.3, R9.1
D0_TX: R24.1, U1.10
D1_IN: C15.1, D6.1, R10.2, R12.2, U4.3
D1_RAW: D15.2, J3.4, Q4.3, R10.1
D1_TX: R26.1, U1.11
D7_A: D7.1, R3.2
D8_K: D8.1, R8.2
D23_K: D23.2, R81.2
EN: C13.1, R4.2, R86.2, U1.45
GND: C1.2, C2.2, C4.2, C5.2, C6.2, C11.2, C12.2, C13.2, C14.2, C15.2, C16.2, C37.2, C41.2, C42.2, C43.2, C44.2, C45.2, D2.2, D5.2, D6.2, D7.2, D15.3, D16.3, D19.3, D24.2, D25.2, J1.13, J1.14, J1.A1B12, J1.B1A12, J3.2, Q1.2, Q2.2, Q3.2, Q4.2, R1.2, R2.2, R13.2, R14.2, R25.2, R27.2, R65.2, R87.2, R95.2, SW1.4, SW2.4, U1.1, U1.2, U1.42, U1.43, U1.46, U1.47, U1.48, U1.49, U1.50, U1.51, U1.52, U1.53, U1.54, U1.55, U1.56, U1.57, U1.58, U1.59, U1.60, U1.GND, U2.4, U3.2, U4.2, U9.5, U11.2
IO0: R5.2, SW1.1, U1.4
IO21: R8.1, U1.25
IO47: R81.1, U1.27
JP2_A: JP2.1, R68.2
LED_IN: C42.1, D24.1, R20.2, R22.2, U11.1
LED_RX: U1.14, U11.6
LED_TX: R6.1, U1.12
Q1_G: Q1.1, R6.2, R13.1
Q2_G: Q2.1, R7.2, R14.1
Q3_G: Q3.1, R24.2, R25.1
Q4_G: Q4.1, R26.2, R27.1
RDR_BEEP: D16.2, J3.6, Q2.3, R21.1
RDR_LED: D16.1, J3.5, Q1.3, R20.1
RS485_A: D19.1, J3.7, R68.1, R88.1
RS485_B: D19.2, J3.8, JP2.2, R89.1
RS485_DE: R65.1, U1.34, U9.2, U9.3
RS485_DI: U1.39, U9.4
RS485_RO: R75.1, U1.40, U9.1
RST_MR: C45.1, SW2.1, U3.3
U2_BST: C3.1, U2.6
U2_SW: C3.2, L1.1, U2.5
U3_RST: R86.1, U3.1
U9_A: R88.2, U9.6
U9_B: R89.2, U9.7
USB_DN: J1.A7, J1.B7, U1.23
USB_DP: J1.A6, J1.B6, U1.24
VBUS: C6.1, D3.2, J1.A4B9, J1.B4A9, R87.1
WG_D0: U1.8, U4.6
WG_D1: U1.9, U4.4

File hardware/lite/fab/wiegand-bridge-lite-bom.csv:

Comment,Designator,Footprint,LCSC Part #
10u,"C1,C2",C_1206_3216Metric,C13585
22u,C11,C_0603_1608Metric,C59461
1u,C13,C_0603_1608Metric,C15849
100p,"C14,C15,C42,C43",C_0603_1608Metric,C14858
100n,"C3,C12,C16,C37,C41,C44",C_0603_1608Metric,C14663
22u,"C4,C5",C_0805_2012Metric,C45783
10n,C45,C_0603_1608Metric,C57112
10u,C6,C_0805_2012Metric,C15850
SS56,D1,SMA_L4.3-W2.6-LS5.0-RD,C18199169
SM712,"D15,D16,D19",SOT-23-3_L3.0-W1.7-P0.95-LS2.9-BR,C32677
SMAJ18CA,D2,SMA_L4.3-W2.6-LS5.0-BI,C19077539
BAT54,D26,SOT-23-3_L2.9-W1.4-P1.90-LS2.5-BR,C22466368
SS34,D3,SMA_L4.3-W2.6-LS5.2-RD,C8678
MMSZ5231B,"D5,D6,D24,D25",SOD-123_L2.8-W1.6-LS3.7-RD,C19077422
green LED,"D7,D23",LED0805-R-RD,C2297
red,D8,LED0805-RD,C84256
0.5A 24V,F1,F1812,C516067
USB-C,J1,USB-C-SMD_TYPE-C-16PIN-2MD-073,C2765186
12V GND D0 D1 LED BEEP A B,J3,CONN-TH_8P-P3.50_KF2EDGR-3.5-8P,C441177
4.7uH,L1,IND-SMD_L5.0-W5.0,C305174
AO3400A,"Q1,Q2,Q3,Q4",SOT-23-3_L2.9-W1.3-P1.90-LS2.4-BR,C20917
5.1k,"R1,R2",R_0603_1608Metric,C23186
22k,"R11,R12,R22,R23",R_0603_1608Metric,C31850
100,"R6,R7,R24,R26",R_0603_1608Metric,C22775
100k,"R13,R14,R25,R27",R_0603_1608Metric,C25803
470,"R3,R81",R_0603_1608Metric,C23179
10k,"R4,R5,R65,R75",R_0603_1608Metric,C25804
120,R68,R_0603_1608Metric,C22787
1k,"R8,R9,R10,R20,R21,R86,R87",R_0603_1608Metric,C21190
10,"R88,R89",R_0603_1608Metric,C844519
4.7k,R95,R_0603_1608Metric,C23162
TS-1187A tact switch,"SW1,SW2",SW-SMD_4P-L5.1-W5.1-P3.70-LS6.5-TL_H1.5,C318884
ESP32-S3-MINI-1-N4R2,U1,BULETM-SMD_ESP32-S3-MINI-1-N8,C3013941
AP63203,U2,TSOT-26_L2.9-W1.6-P0.95-LS2.8-BL,C780769
TPS3808G30,U3,SOT-23-6_L2.9-W1.6-P0.95-LS2.8-BR,C189211
SN74LVC2G17 Schmitt buffer,"U4,U11",SOT-23-6_L2.9-W1.6-P0.95-LS2.8-BL,C10429
THVD1420,U9,SOIC-8_L4.9-W3.9-P1.27-LS6.0-BL,C3235215

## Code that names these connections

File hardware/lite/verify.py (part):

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FAB = os.path.join(HERE, "fab")
# Every module GPIO the netlist wires, and the net it must be on. The YAML must claim each one
# (the firmware is the only thing that sets a pin's boot-time state), and must name no other.
EXPECT_GPIO = {4: "WG_D0", 5: "WG_D1", 6: "D0_TX", 7: "D1_TX", 8: "LED_TX", 9: "BEEP_TX", 10: "LED_RX",
               11: "BEEP_RX", 21: "IO21", 47: "IO47", 38: "RS485_DE", 43: "RS485_DI", 44: "RS485_RO"}
IMPLICIT_GPIO = {19: "USB_DN", 20: "USB_DP", 0: "IO0"}       # used by the USB-JTAG console and the ROM, not named in YAML
# Module pads that are meant to be open (every other U1 pad must carry a net): IO1/IO2 (5, 6), IO3 (7),
# IO12-IO18 (16-22), IO26 (26, PSRAM), IO33-IO37 and IO48 (28-33), IO39-IO42 (35-38), IO45 (41),
# IO46 (44). Pads 42/43 are GND on the module, so they are wired.
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
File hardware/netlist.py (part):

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    "28": "ETH_MISO", "29": "ETH_CS", "30": "ETH_INT", "31": "RS485_DE", "32": "EXP_INT", "33": "IO40",   # IO40 = reader BEEP since rev 10 (IO7 could not be routed out)
    "34": "I2C_SDA", "35": "I2C_SCL", "36": "RS485_RXD", "37": "RS485_DI",
    "39": "BAT_SENSE", "40": "GND", "41": "GND"})
# 16 IO46, 26 IO45: strapping, no connect (15 IO3 is TEMP_ADC). 38 IO2: free since rev 12 (reader monitor on I2C).
cap("C11", "22u6", "+3V3")
cap("C12", "100n", "+3V3")
res("R4", "10k", "+3V3", "EN")
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part("U13", "vson10_ep", "TPS26625", "C2862873",
     {"1": "BOOST_SNS", "2": "U13_UVLO", "3": "GND", "4": "RDR_EN", "5": "GND", "6": "GND",
      "7": "U13_ILIM", "8": "U13_DVDT", "9": "RDR_FLT", "10": "RDR_SW", "11": "GND"})
cap("C41", "100n", "BOOST_SNS")                 # U13 IN, at the pin
cap("C43", "100n", "RDR_SW")                    # U13 OUT, >= 0.01 uF (TI)
# ILIM: 26.7k -> 0.237-0.257 A (TI's table, -40..125 C). Above the reader's 0.2 A at 9 V; as low as the
# cell loop allows on battery.
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part("Q13", "sot6br", "FS8205A", "C2830320",
     {"1": "BAT-", "2": "Q6_D", "3": "GND", "4": "OC", "5": "Q6_D", "6": "OD"})
# battery-path study (2026-10-29): DMP2035U (<= 45 mohm at -2.5 V, <= 62 at -1.8 V; the AO3401A gave no
# figure below -2.5 V and VSYS sags toward 2 V in a reader fault on battery). Same SOT-23 pinout.
part("Q5", "sot23_ao3401", "DMP2035U", "C110499", {"1": "+5V", "2": "VSYS", "3": "BAT+"})
# R27 10k (audit round 8, S4; was 100k): with external power gone, it holds +5V, Q5's gate, low against
# D11's reverse leakage (SS34: ~75 uA typical at 75 C, only 0.5 mA at 40 V guaranteed), so Q5 keeps
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res("R60", "10k", "EXP_INT", "+3V3")
res("R61", "100k", "CHRG", "+3V3")       # CHRG also sinks D12 (from +5V); reads ~3.3 V when idle
res("R62", "100k", "DONE_N", "+3V3")
# spare expander pins tied low (datasheet: unused I/O to VCC or GND through ~10k); ETH_RST pulled up
# RN1-1 also holds DISP_RST low, so a fitted TFT stays in reset until firmware drives P06
for ref, nets in (("RN1", ("DISP_RST", "EXP07", "EXP10", "EXP11")), ("RN2", ("EXP12", "EXP13", "EXP14", "EXP15")),
                  ("RN3", ("EXP16", None, None, None))):   # EXP17: no room to route; firmware drives it low
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part("K1", "relay", "SRD-05VDC-SL-C", None,
     {"1": "+5V", "4": "RELAY_COIL", "5": "RELAY_COM", "2": "RELAY_NO", "3": "RELAY_NC"})  # coil 1-4, COM 5, NO 2, NC 3
part("J15", "kf128", "RELAY NC NO", None, {"1": "RELAY_NC", "2": "RELAY_NO"})   # top to bottom: NO, NC
part("J16", "kf128", "RELAY COM", None, {"2": "RELAY_COM"})   # then COM; pin 1 spare

# --- Block 14 (rev 10): RS-485 / OSDP on UART0 ----------------------------------------------------
# rev 12: THVD1420 (full fail-safe receiver), so this node needs no bias of its own
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

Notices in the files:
hardware/lite/verify.py:
SPDX-FileCopyrightText: 2026 edgecoil
SPDX-License-Identifier: MIT
hardware/netlist.py:
SPDX-License-Identifier: CERN-OHL-S-2.0
